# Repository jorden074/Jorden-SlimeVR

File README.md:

# Jorden-SlimeVR
This repository contains all my open-source tracker designs, and their corresponding firmware. All of which are licensed under CERN-OHL-S to encourage other free, open-source designs. All designs are made with open-source tools as to be edited by anyone.

## Software
- FreeCAD
- KiCAD
- Blender

## Marathon-1 *WIP*
### Overview
Seed Studio XIAO nRF52840 based 'smol' tracker with an oversized battery for those who can never remember to charge their trackers... <3

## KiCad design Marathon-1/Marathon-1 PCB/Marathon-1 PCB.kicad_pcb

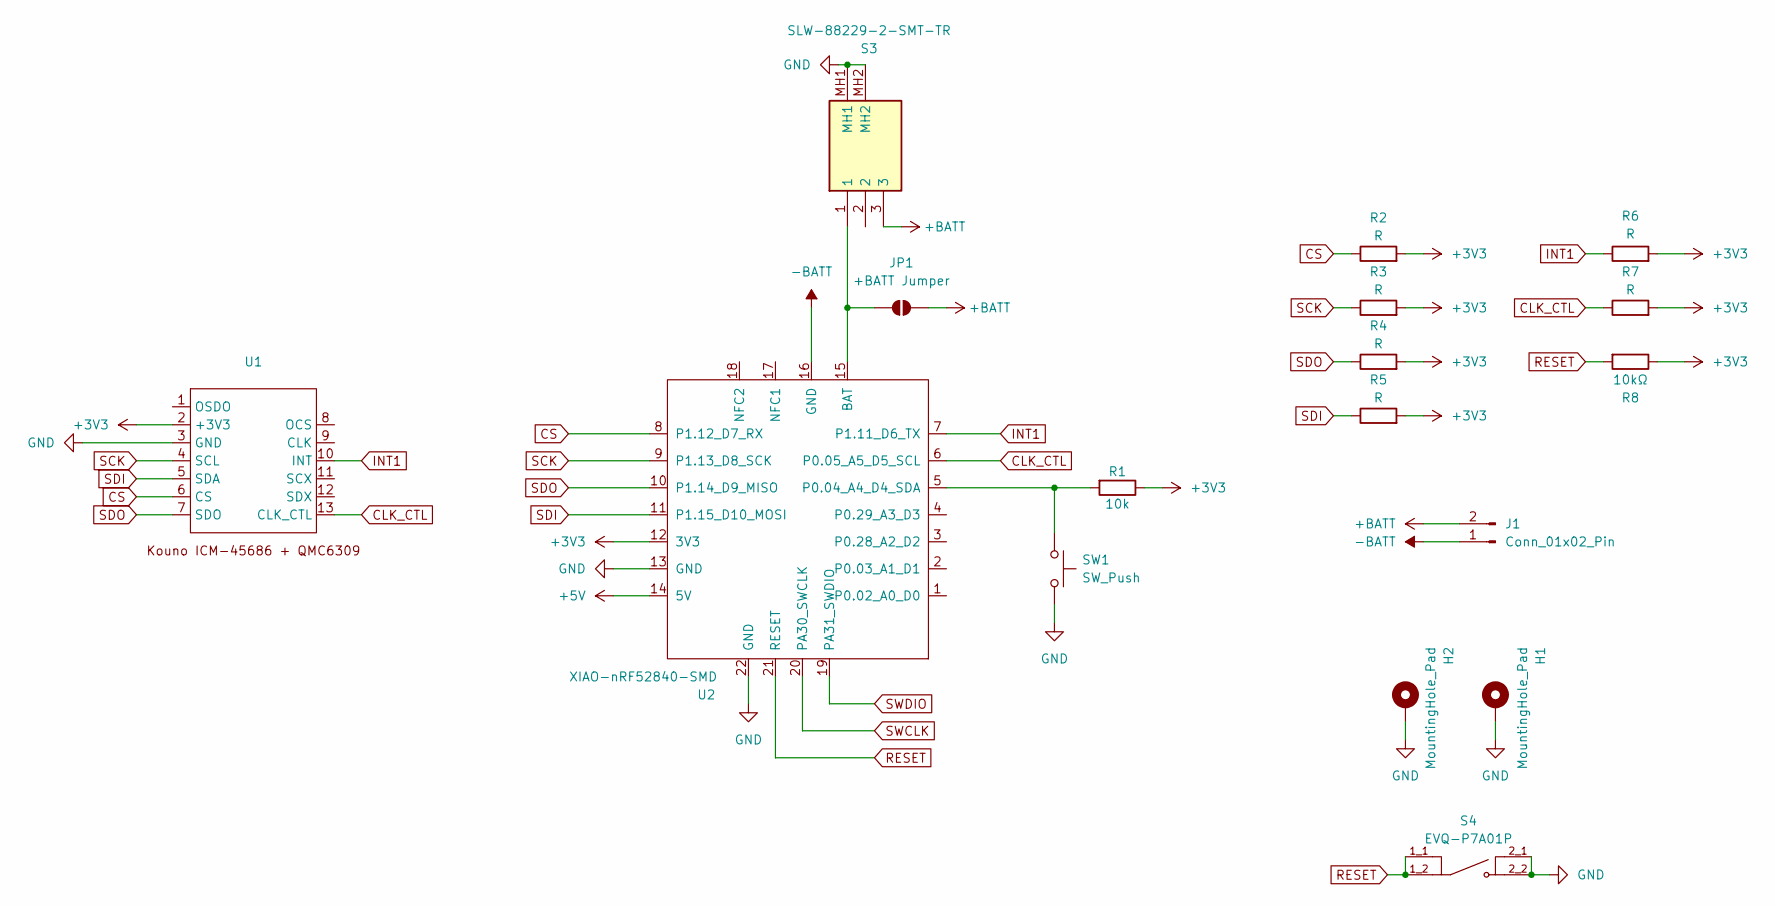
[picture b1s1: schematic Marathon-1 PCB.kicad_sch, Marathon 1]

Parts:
H1, H2: MountingHole_Pad; MountingHole_2.2mm_M2_DIN965_Pad
J1: Conn_01x02_Pin; PinHeader_1x02_P2.00mm_Vertical
JP1: +BATT Jumper; SolderJumper-2_P1.3mm_Open_RoundedPad1.0x1.5mm
R1: 10k; R_0603_1608Metric
R2, R3, R4, R5, R7: R; R_0603_1608Metric
R6: R; C_0603_1608Metric
R8: 10kΩ; R_0603_1608Metric
S3: SLW-88229-2-SMT-TR; SLW882292SMTTR; Mouser Part Number 179-SLW-88229-2SMTTR
S4: EVQ-P7A01P; SW_EVQ-P7A01P
SW1: SW_Push; SW_SPST_CK_KMS2xxGP
U1: Kouno ICM-45686 + QMC6309 Module
U2: XIAO-nRF52840-SMD

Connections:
+3V3: R1.1, R2.2, R3.2, R4.2, R5.2, R6.2, R7.2, R8.1, U1.2 (+3V3), U2.12 (3V3)
+5V: U2.14 (5V)
+BATT: J1.2, JP1.2 (B), S3.3
-BATT: J1.1, U2.16 (GND)
CLK_CTL: R7.1, U1.13 (CLK_CTL), U2.6 (P0.05_A5_D5_SCL)
CS: R2.1, U1.6 (CS), U2.8 (P1.12_D7_RX)
GND: H1.1, H2.1, S3.MH1, S3.MH2, S4.2_1, S4.2_2, SW1.2, U1.3 (GND), U2.13 (GND), U2.22 (GND)
INT1: R6.1, U1.10 (INT), U2.7 (P1.11_D6_TX)
unnamed: JP1.1 (A), S3.1, U2.15 (BAT)
unnamed: R1.2, SW1.1, U2.5 (P0.04_A4_D4_SDA)
RESET: R8.2, S4.1_1, S4.1_2, U2.21 (RESET)
SCK: R3.1, U1.4 (SCL), U2.9 (P1.13_D8_SCK)
SDI: R5.1, U1.5 (SDA), U2.11 (P1.15_D10_MOSI)
SDO: R4.1, U1.7 (SDO), U2.10 (P1.14_D9_MISO)
SWCLK: U2.20 (PA30_SWCLK)
SWDIO: U2.19 (PA31_SWDIO)

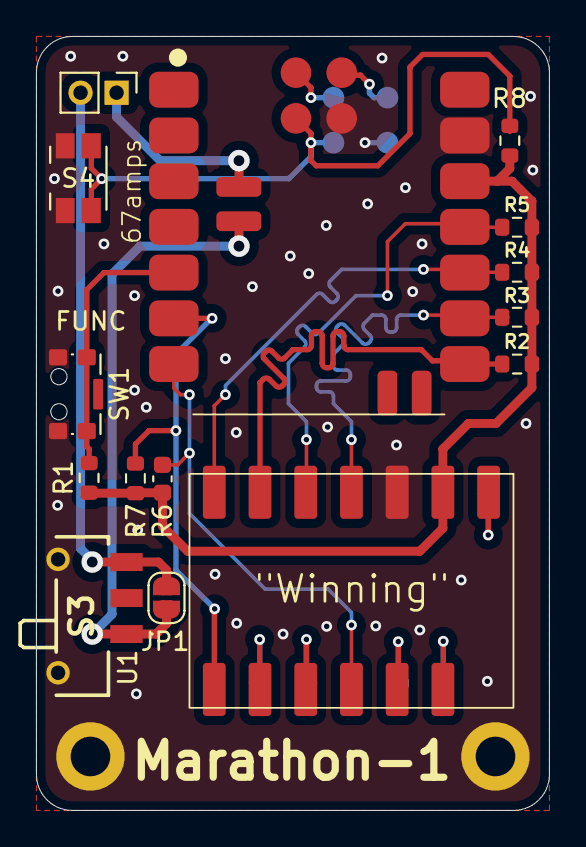
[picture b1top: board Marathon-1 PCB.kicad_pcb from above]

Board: 2 copper layers, 28.5 x 43.0 mm, 17 parts (0 on the bottom side), 13 nets.

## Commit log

2025-09-26 Add CERN-OHL-S license.
2025-09-26 Initial Marathon-1 Push
2025-09-30 Adjusted overhanging silkscreen on nRF
2025-09-30 DRC warnings cleared
    Silkscreen warnings cleared
2025-09-30 Silkscreen Adjusted
    :3 moved up
2025-09-30 Add gitignore
    ignore .lck files
2025-09-30 remove .lck file from prior to gitignore
2025-09-30 Rename .gitignore.txt to .gitignore
    .txt gitignore.... fml lmao
2025-09-30 Add Marathon-1 Render 1 image asset
    Added a new PNG image 'Marathon-1 Render 1.png' to the Assets directory
2025-09-30 Update README with project details and software list
    Added information about open-source tracker designs, licensing under CERN-OHL-S, and listed FOSS programs used (FreeCAD, KiCAD, Blender) for design and editing.
2025-09-30 Replace PNG with JPEG and update README image
    Removed the old PNG render and added a new JPEG render for Marathon-1. Updated README to reference the new image and added a section for Marathon-1 under Trackers.
2025-09-30 Update README formatting and add Marathon-1 overview
    Fixed spacing in the Software section header and added an overview for the Marathon-1 tracker, providing more context about its hardware and intended use.
2025-09-30 Update Marathon-1 section in README
    Renamed 'Trackers' section to 'Marathon-1 WIP' and updated formatting to clarify the project's status.
2025-09-30 Emphasize 'WIP' in Marathon-1 section
    Updated the README to bold the 'WIP' label in the Marathon-1 section for better visibility.
2025-09-30 Update formatting for Marathon-1 section in README
    Changed bold formatting from double asterisks to double underscores for the 'WIP' label in the Marathon-1 section to improve consistency.
2025-09-30 Add CAD screenshot and update README formatting
    Added Marathon1-CAD-Screenshot.png to Assets and updated README.md to improve wording and include the new screenshot image for better documentation.
2025-09-30 Remove unused image from README
    Deleted a redundant CAD screenshot image reference from the README to improve clarity and focus on the main render image.
2025-10-06 Add *.FCBak to .gitignore
    Added the *.FCBak pattern to .gitignore to exclude backup files from version control.
2025-10-06 Update CAD and PCB files, remove backups and locks
    Deleted an old FreeCAD backup and KiCad lock file, updated the main FreeCAD housing file, and added a new PCB backup zip. These changes help maintain current design files and remove unnecessary or te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
2025-10-06 Update PCB project settings and add backup
    Changed active layer and high contrast mode settings in Marathon-1 PCB.kicad_prl. Added a new project backup ZIP file for Marathon-1 PCB dated 2025-10-05.
2025-10-10 Adjusted Model
    Board pocket tolerances have been increased by 0.3mm.
    MFB protrusion removed and pusher extension added to internal face.
2025-10-10 Update M1 Housing CAD model
2025-10-10 advanced shown state in parts.
2025-10-27 No idea... just need a place to restore to in a second
2025-10-27 The faceplate offset dimension has been replaced with an absolute dimension
2025-11-02 Lower edge loop fillet increased
    0.5mmr to 1.25mmr—poor print performance fix

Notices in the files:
Marathon-1/Marathon-1 PCB/Marathon-1 PCB.kicad_pcb:
© Jorden074 2025
